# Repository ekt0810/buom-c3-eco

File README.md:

# Bướm C3 ECO

Hồ sơ prototype bướm vỗ cánh điều khiển tay bằng **XIAO ESP32-C3 + ESP-NOW**. Dự toán **3.865.000 đồng** gồm bướm, tay phát tự ráp, bộ sạc, nguồn cho sạc và 400.000 đồng dự phòng; chưa gồm dụng cụ hàn/đo. Giá và khối lượng là dự toán tại thời điểm lập hồ sơ ngày 12/11/2026.

**Chưa thử bay trên phần cứng thật.** Mạch, firmware và mô phỏng đã được kiểm tra ở mức được ghi trong báo cáo; khả năng nâng và bay cần đo trên mẫu chế tạo. Bản ECO không có IMU; PID và bám đường trong mô phỏng là phần nghiên cứu nâng cấp.

## Tải và bắt đầu

- [Tải toàn bộ hồ sơ ZIP](outputs/Buom_C3_ECO_duoi_4_trieu.zip?raw=true)
- [Hướng dẫn chế tạo PDF — 9 trang](outputs/buom_c3_eco/HUONG_DAN_CHE_TAO.pdf)
- [BOM Excel](outputs/buom_c3_eco/BOM_Buom_C3.xlsx) · [BOM CSV](outputs/buom_c3_eco/BOM.csv)
- [Đọc trước khi mua linh kiện](outputs/buom_c3_eco/README.md)
- [Báo cáo kiểm tra và giới hạn](outputs/buom_c3_eco/verification/FINAL_CHECKS.md)

## Nội dung

| Thư mục | Nội dung |
|---|---|
| [hardware](outputs/buom_c3_eco/hardware) | Schematic, PCB KiCad 10, PDF, Gerber và Excellon; carrier PCB là tùy chọn |
| [firmware_eco](outputs/buom_c3_eco/firmware_eco) | Mã Arduino cho bướm XIAO ESP32-C3 và tay phát ESP32 DevKit |
| [pid_reference](outputs/buom_c3_eco/pid_reference) | PID thuần C++ tham khảo cho nghiên cứu nâng cấp |
| [matlab](outputs/buom_c3_eco/matlab) | Mô hình MATLAB, bốn kịch bản đã chạy bằng Octave và dữ liệu kết quả |
| [viewer](outputs/buom_c3_eco/viewer) | Trình xem Three.js/WebGL 3D, thư viện đi kèm để chạy cục bộ |
| [images](outputs/buom_c3_eco/images) | Ảnh concept, sơ đồ đấu dây và ảnh xem trước |
| [verification](outputs/buom_c3_eco/verification) | Log compile, ERC/DRC, kiểm tra netlist, PID/protocol và viewer |

Firmware giao mặc định khóa actuator. Đọc hướng dẫn để điền MAC, đổi khóa ghép đôi mẫu, hiệu chuẩn nguồn/xung–góc, kiểm tra chiều servo và mất link trước khi lắp cánh.

## Chạy mô phỏng và xem 3D

Trong MATLAB, chuyển vào thư mục `outputs/buom_c3_eco/matlab` rồi chạy `run_all`. Mã không cần toolbox; kết quả đi kèm được chạy trên **GNU Octave 11.3.0**, chưa chạy trực tiếp bằng MATLAB. Hệ số khí động đang là giả định; mô hình có thông tin vị trí/độ cao lý tưởng mà phần cứng ECO không có.

Với Python 3, chạy từ thư mục gốc repo:

```sh
python outputs/buom_c3_eco/start_viewer.py
```

Trình xem tự mở tại `http://127.0.0.1:8765/viewer/`, animation tự chạy. Đây là phát lại dữ liệu mô phỏng; không phải bằng chứng mẫu thật có thể bay theo đường đó.

## Kiểm tra đã thực hiện

KiCad ERC 0 lỗi/0 cảnh báo; DRC 0 vi phạm và 0 pad chưa nối theo cấu hình kiểm tra đi kèm; đối chiếu 89 chân giữa schematic và PCB. Hai firmware đã biên dịch với Arduino-ESP32 3.3.3. Kiểm tra C++ điều khiển/protocol, bốn kịch bản Octave và viewer Edge/WebGL2 đã chạy. Các mục bỏ qua trong ERC/DRC được giữ trong file báo cáo.

[SHA256SUMS.txt](outputs/buom_c3_eco/SHA256SUMS.txt) ghi hash các file bàn giao, với đường dẫn tính từ `outputs/buom_c3_eco/`. ZIP đã được kiểm tra CRC và đối chiếu nội dung với bản thư mục.

## Nguồn cơ khí và giấy phép

Tham khảo hình học [ESP-FLUTTER của Max Imagination](https://github.com/maximagination1/ESP-FLUTTER). **File cơ khí STL có phí không nằm trong repo**; mua từ tác giả theo link trong hướng dẫn. Khoản dự toán file/in đã có trong BOM. Repo không phân phối firmware gốc của dự án tham khảo.

Xem [THIRD_PARTY.md](outputs/buom_c3_eco/THIRD_PARTY.md) và các thông báo giấy phép đi kèm cho KiCad Libraries và Three.js. Chỉ hồ sơ bàn giao và mã nguồn dự án được đưa lên đây; bộ cài, cache và file làm việc tạm không thuộc gói.

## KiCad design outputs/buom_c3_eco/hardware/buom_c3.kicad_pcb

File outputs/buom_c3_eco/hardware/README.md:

# Carrier Rev A, dùng được cho cấu hình ECO

- Kích thước 60 x 40 mm; 2 lớp; FR4 0,8 mm; 1 oz; mạ lỗ xuyên; bề mặt HASL không chì hoặc ENIG.
- XIAO hàn castellated trên 14 pad biên. Các pad BAT/debug phía đáy được bỏ có chủ ý. USB quay ra mép ngắn theo silkscreen.
- Module buck gắn ngoài qua J2. J2 không phải footprint trực tiếp của Mini-360 hoặc Pololu.
- ECO **không lắp** J3/J4/J7/Q3/R7/R8, không lắp IMU, RP1 hoặc LED. Giữ tất cả mạch nguồn, PWM và đo pin.
- J1/J2/J5/J6 có thể hàn dây trực tiếp thay header để nhẹ. Dây phải có chống kéo và kiểm tra cực. Không lấy dòng servo qua chân 5V của XIAO.
- Pad vuông là pin 1. Servo: 1=GND, 2=VSERVO, 3=PWM. Pin JST/servo ngoài thực tế phải đối chiếu, không tin màu dây.
- Q1 AO4407A S=1/2/3, G=4, D=5/6/7/8. Q2 2N7002 G=1 S=2 D=3. D1 SS14 pin1 cathode, pin2 anode.
- U2 AHCT2G125DP pin1/7=OE thấp; pin2/5=A; pin6/3=Y; pin4=GND; pin8=5V.
- C5 220uF/16V low ESR: pin1 dương, pin2 âm, đường kính thân <=6,3mm, bước chân 2,5mm.
- Đường power 1mm tối thiểu; các via chuyển lớp chính rail VSERVO được gia cường. DRC không chứng minh khả năng chịu dòng/nhiệt; đo dưới tải servo thật trước bay.
- Không có chống ngược cực. Rút pin để ngắt điện vật lý. D1 chỉ ngăn nguồn USB cấp ngược vào bus 5V bên ngoài.
- File dự án chứa cả vị trí linh kiện mở rộng để có thể dùng khi nghiên cứu PID sau. BOM chính ghi số lượng 0 cho phần bỏ lắp.

`fabrication/` dùng để gửi xưởng khi chọn làm carrier. Chỉ gửi bộ Gerber/Excellon cùng revision; không trộn với Gerber tác giả ESP-FLUTTER.

`design.json` là bảng tham chiếu Refdes/pad/net/placement. Net trong KiCad có tiền tố `/` do net local ở sheet gốc.

Thư viện `Buom.kicad_sym` và `Buom.pretty` cùng `sym-lib-table` / `fp-lib-table` cần giữ cạnh project.

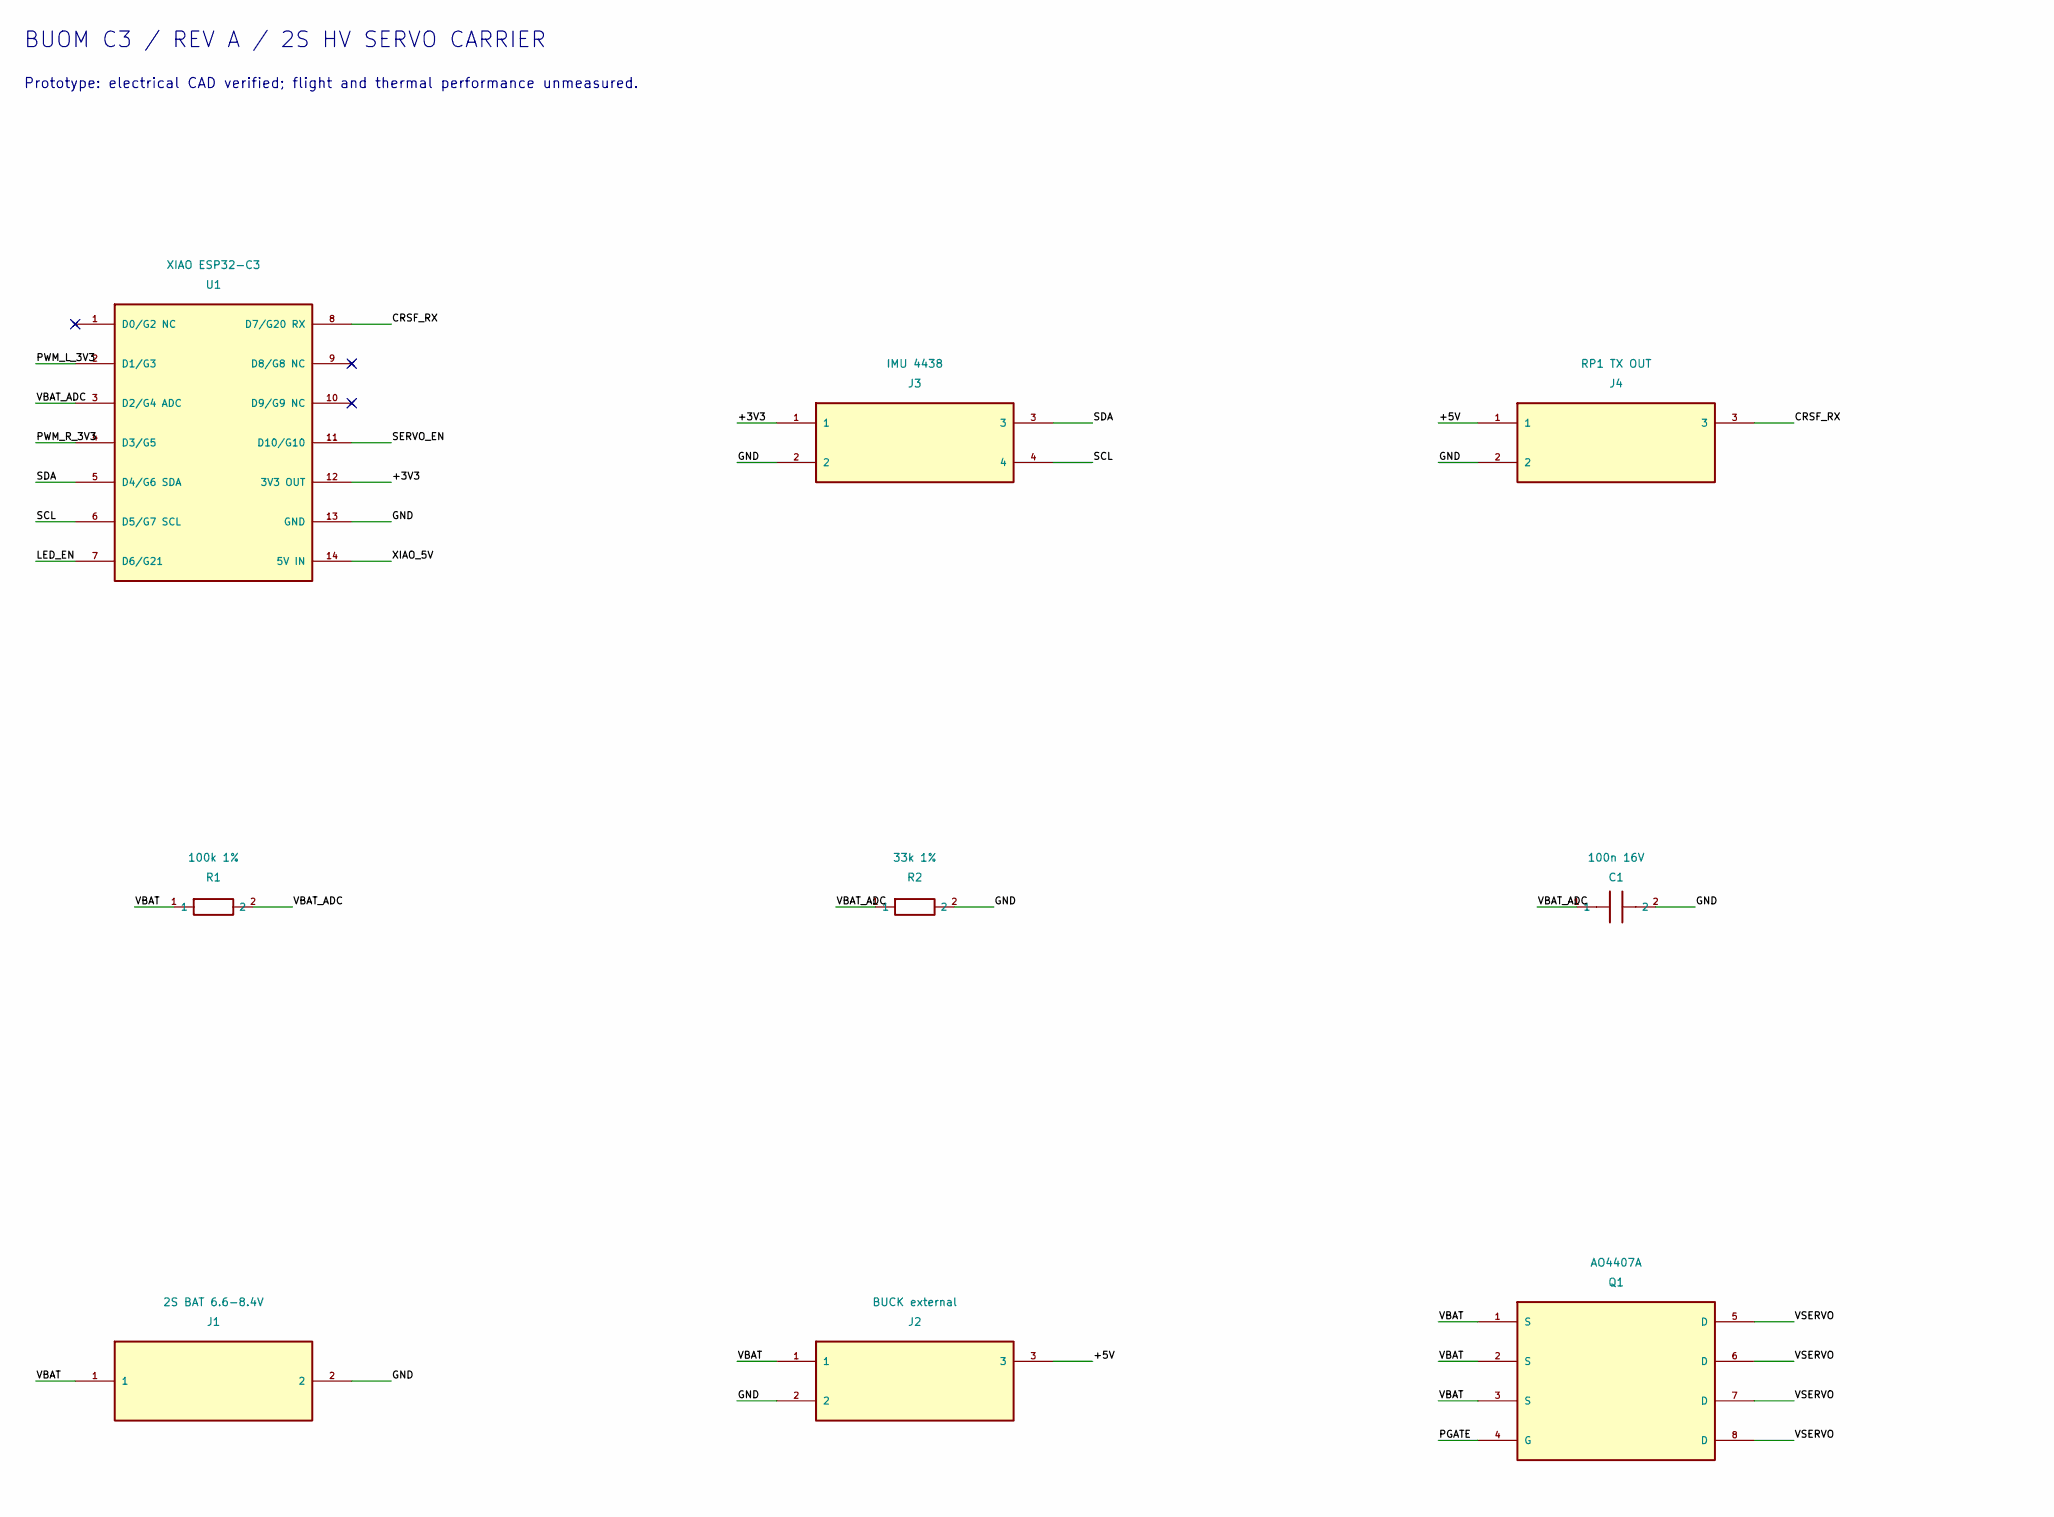
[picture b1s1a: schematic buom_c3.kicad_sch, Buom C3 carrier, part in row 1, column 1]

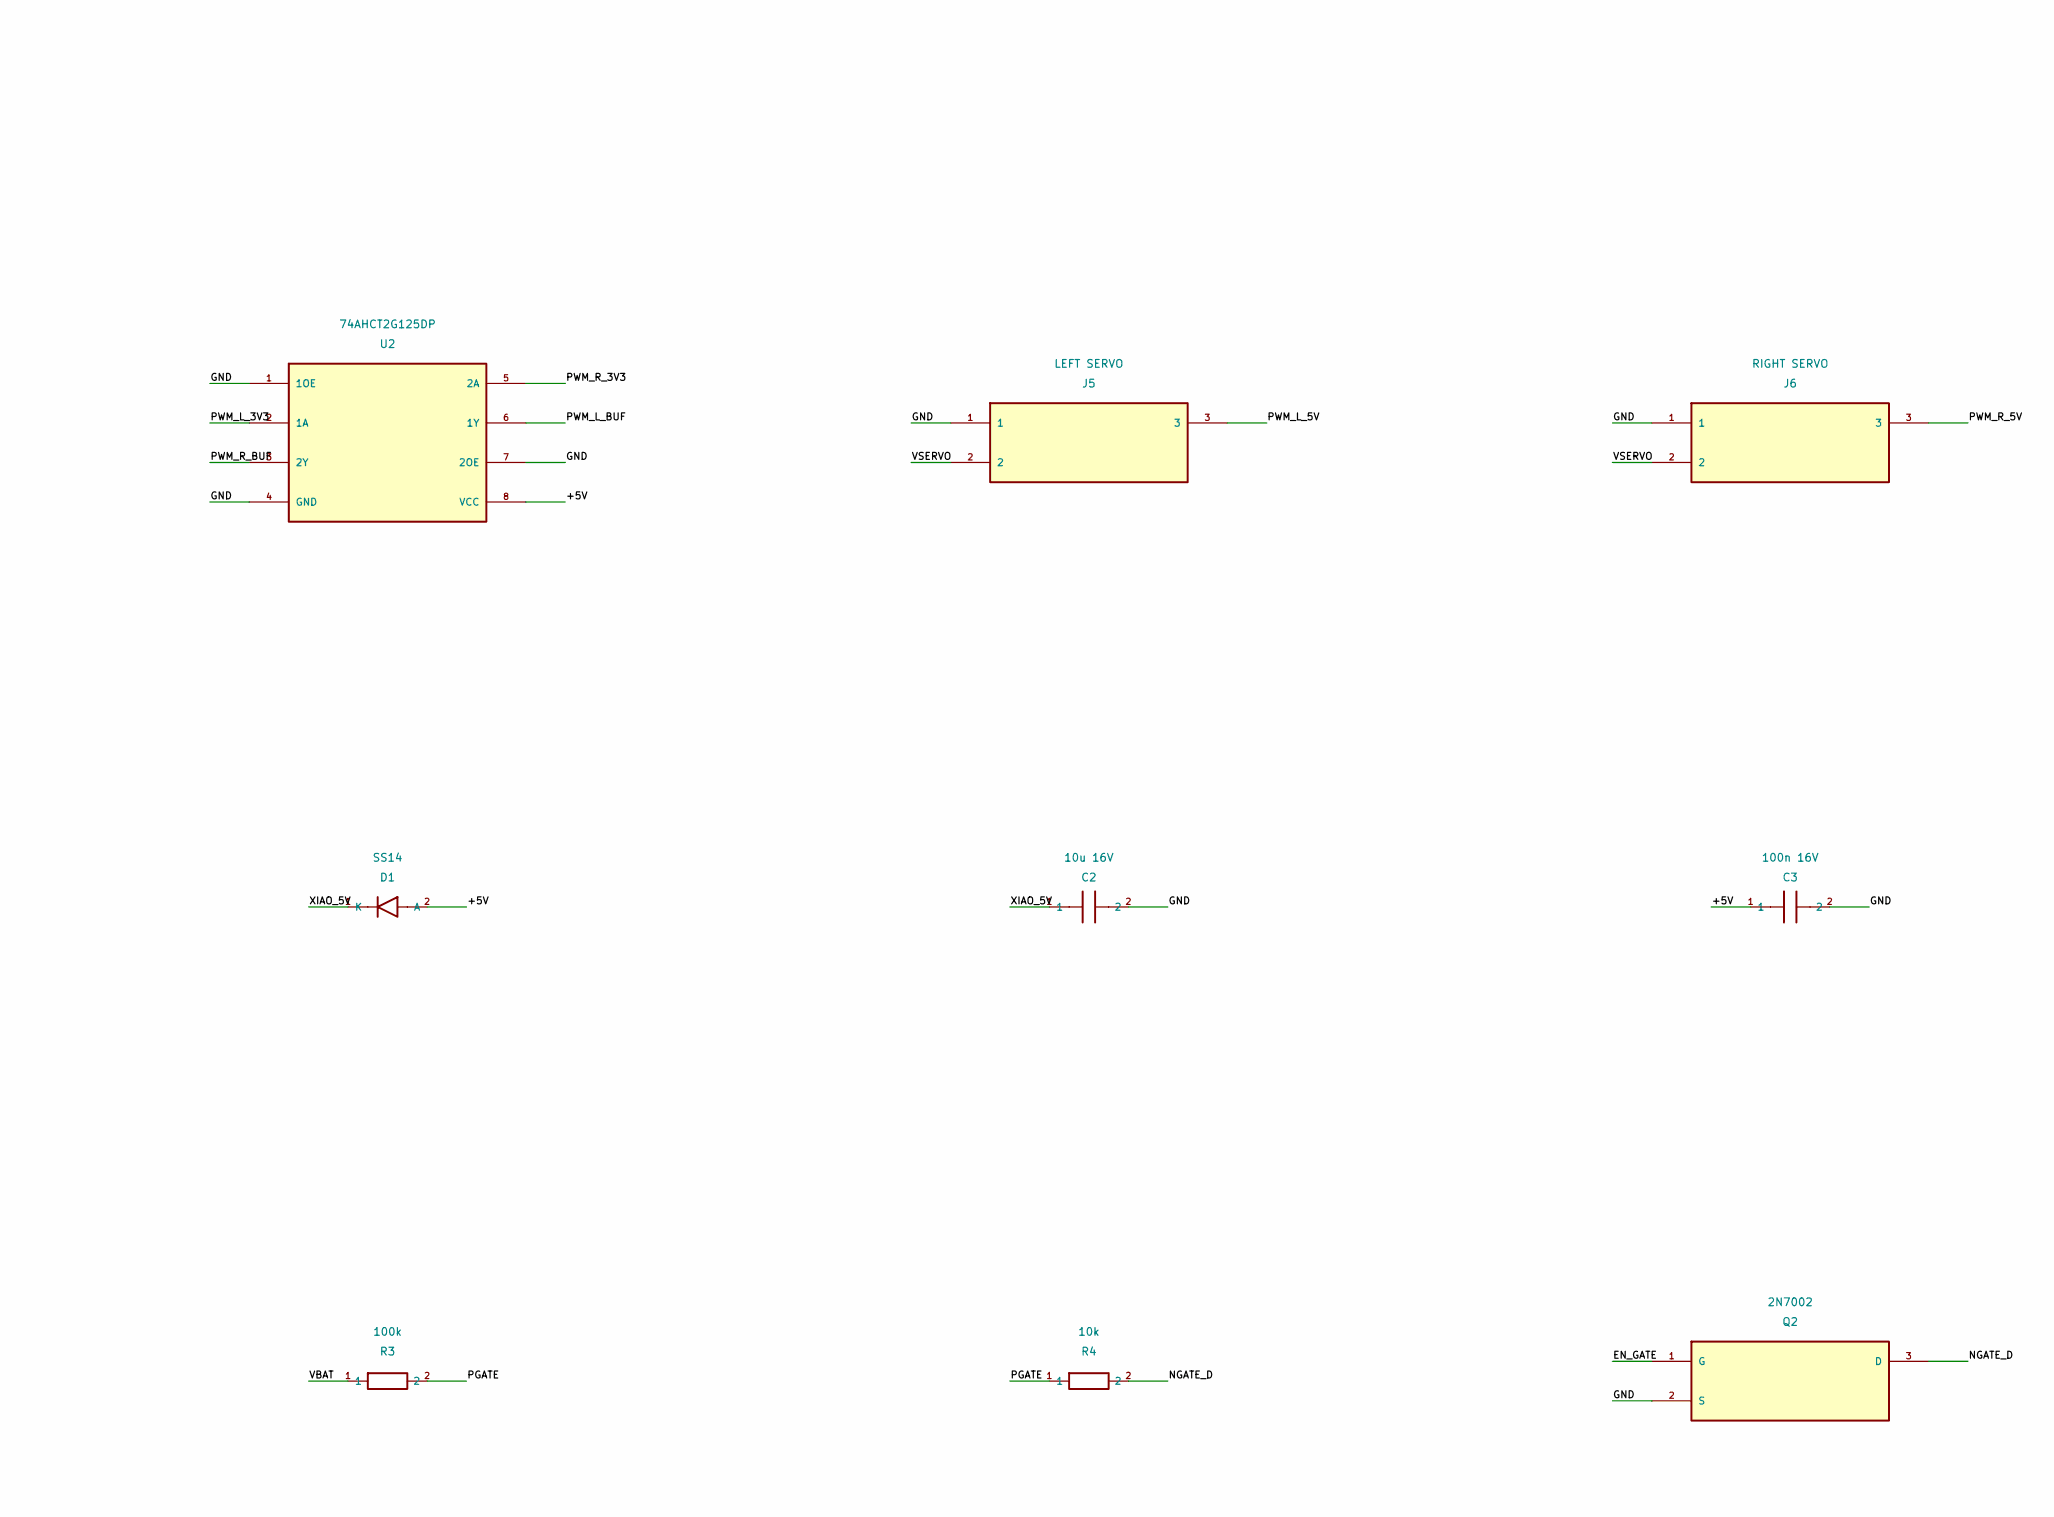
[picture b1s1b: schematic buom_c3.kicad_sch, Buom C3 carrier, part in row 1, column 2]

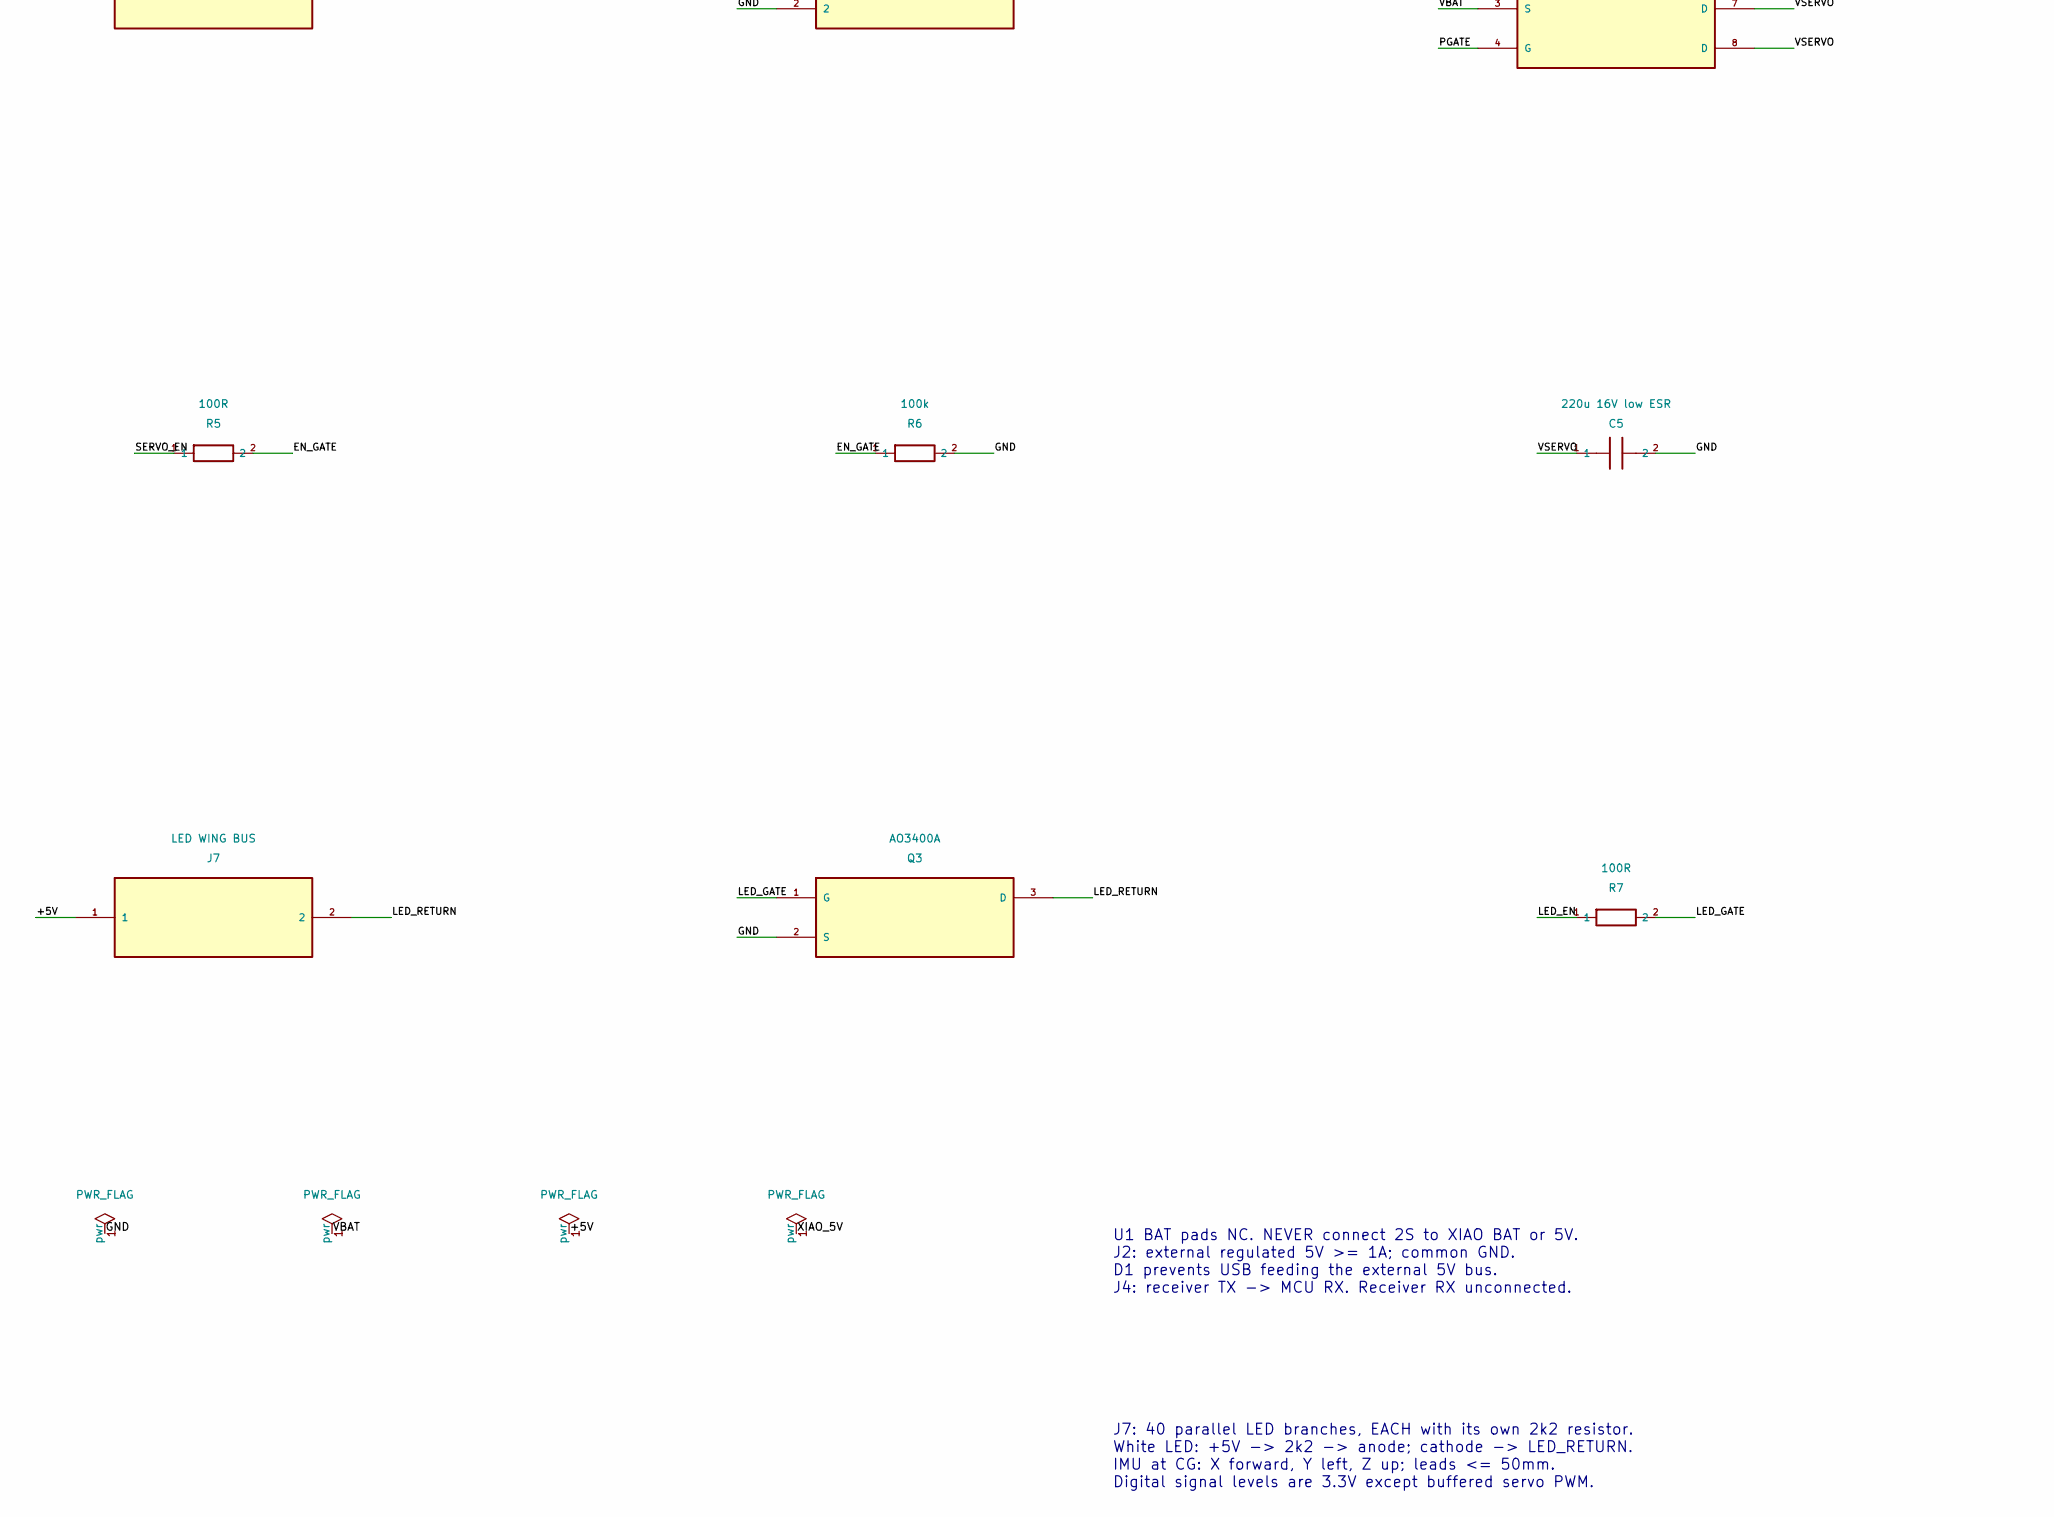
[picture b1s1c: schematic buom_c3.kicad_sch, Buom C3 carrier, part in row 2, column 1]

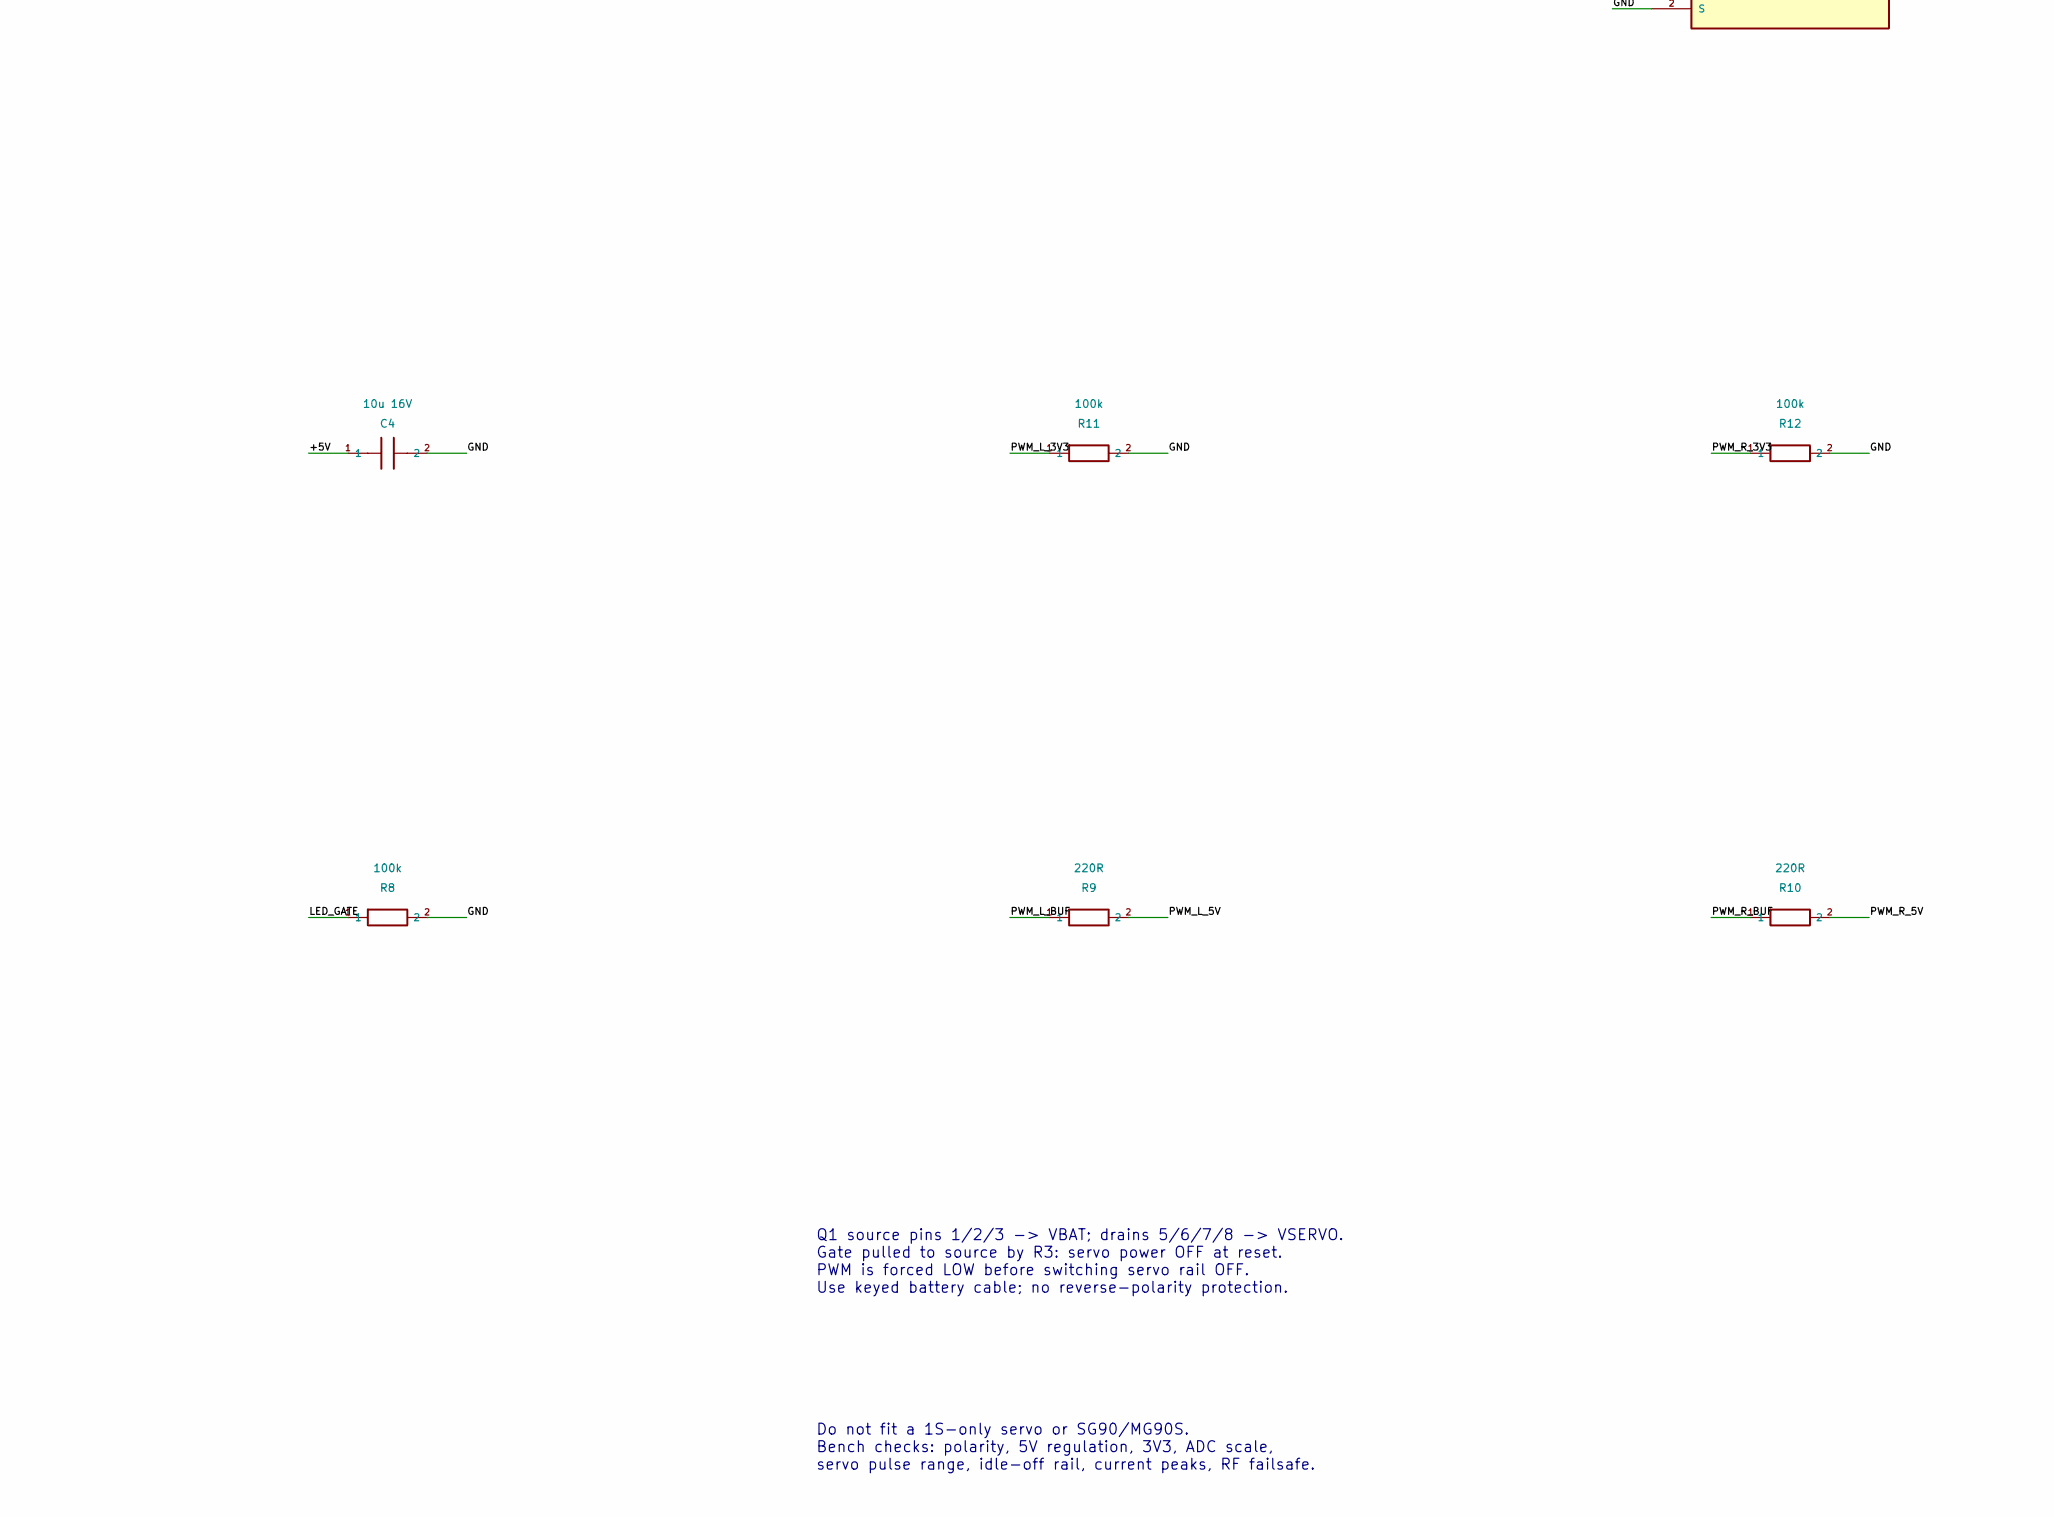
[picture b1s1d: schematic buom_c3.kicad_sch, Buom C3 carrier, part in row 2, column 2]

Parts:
C1, C3: 100n 16V; C_0805_2012Metric
C2, C4: 10u 16V; C_0805_2012Metric
C5: 220u 16V low ESR; CP_Radial_D6.3mm_P2.50mm
D1: SS14; D_SMA
J1: 2S BAT 6.6-8.4V; PinHeader_1x02_P2.54mm_Vertical
J2: BUCK external; PinHeader_1x03_P2.54mm_Vertical
J3: IMU 4438; PinHeader_1x04_P2.54mm_Vertical
J4: RP1 TX OUT; PinHeader_1x03_P2.54mm_Vertical
J5: LEFT SERVO; PinHeader_1x03_P2.54mm_Vertical
J6: RIGHT SERVO; PinHeader_1x03_P2.54mm_Vertical
J7: LED WING BUS; PinHeader_1x02_P2.54mm_Vertical
Q1: AO4407A; SOIC-8_3.9x4.9mm_P1.27mm
Q2: 2N7002; SOT-23
Q3: AO3400A; SOT-23
R1: 100k 1%; R_0805_2012Metric
R2: 33k 1%; R_0805_2012Metric
R3, R6, R8, R11, R12: 100k; R_0805_2012Metric
R4: 10k; R_0805_2012Metric
R5, R7: 100R; R_0805_2012Metric
R9, R10: 220R; R_0805_2012Metric
U1: XIAO ESP32-C3; MCU_Seeed_C3_top14
U2: 74AHCT2G125DP; TSSOP-8_3x3mm_P0.65mm

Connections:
/+3V3: J3.1, U1.12 (3V3 OUT)
/+5V: C3.1, C4.1, D1.2 (A), J2.3, J4.1, J7.1, U2.8 (VCC)
/CRSF_RX: J4.3, U1.8 (D7/G20 RX)
/EN_GATE: Q2.1 (G), R5.2, R6.1
/GND: C1.2, C2.2, C3.2, C4.2, C5.2, J1.2, J2.2, J3.2, J4.2, J5.1, J6.1, Q2.2 (S), Q3.2 (S), R2.2, R6.2, R8.2, R11.2, R12.2, U1.13 (GND), U2.1 (1OE), U2.4 (GND), U2.7 (2OE)
/LED_EN: R7.1, U1.7 (D6/G21)
/LED_GATE: Q3.1 (G), R7.2, R8.1
/LED_RETURN: J7.2, Q3.3 (D)
/NGATE_D: Q2.3 (D), R4.2
/PGATE: Q1.4 (G), R3.2, R4.1
/PWM_L_3V3: R11.1, U1.2 (D1/G3), U2.2 (1A)
/PWM_L_5V: J5.3, R9.2
/PWM_L_BUF: R9.1, U2.6 (1Y)
/PWM_R_3V3: R12.1, U1.4 (D3/G5), U2.5 (2A)
/PWM_R_5V: J6.3, R10.2
/PWM_R_BUF: R10.1, U2.3 (2Y)
/SCL: J3.4, U1.6 (D5/G7 SCL)
/SDA: J3.3, U1.5 (D4/G6 SDA)
/SERVO_EN: R5.1, U1.11 (D10/G10)
/VBAT: J1.1, J2.1, Q1.1 (S), Q1.2 (S), Q1.3 (S), R1.1, R3.1
/VBAT_ADC: C1.1, R1.2, R2.1, U1.3 (D2/G4 ADC)
/VSERVO: C5.1, J5.2, J6.2, Q1.5 (D), Q1.6 (D), Q1.7 (D), Q1.8 (D)
/XIAO_5V: C2.1, D1.1 (K), U1.14 (5V IN)

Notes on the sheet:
BUOM C3 / REV A / 2S HV SERVO CARRIER
Prototype: electrical CAD verified; flight and thermal performance unmeasured.
U1 BAT pads NC. NEVER connect 2S to XIAO BAT or 5V. J2: external regulated 5V >= 1A; common GND. D1 prevents USB feeding the external 5V bus. J4: receiver TX -> MCU RX. Receiver RX unconnected.
Q1 source pins 1/2/3 -> VBAT; drains 5/6/7/8 -> VSERVO. Gate pulled to source by R3: servo power OFF at reset. PWM is forced LOW before switching servo rail OFF. Use keyed battery cable; no reverse-polarity protection.
J7: 40 parallel LED branches, EACH with its own 2k2 resistor. White LED: +5V -> 2k2 -> anode; cathode -> LED_RETURN. IMU at CG: X forward, Y left, Z up; leads <= 50mm. Digital signal levels are 3.3V except buffered servo PWM.
Do not fit a 1S-only servo or SG90/MG90S. Bench checks: polarity, 5V regulation, 3V3, ADC scale, servo pulse range, idle-off rail, current peaks, RF failsafe.

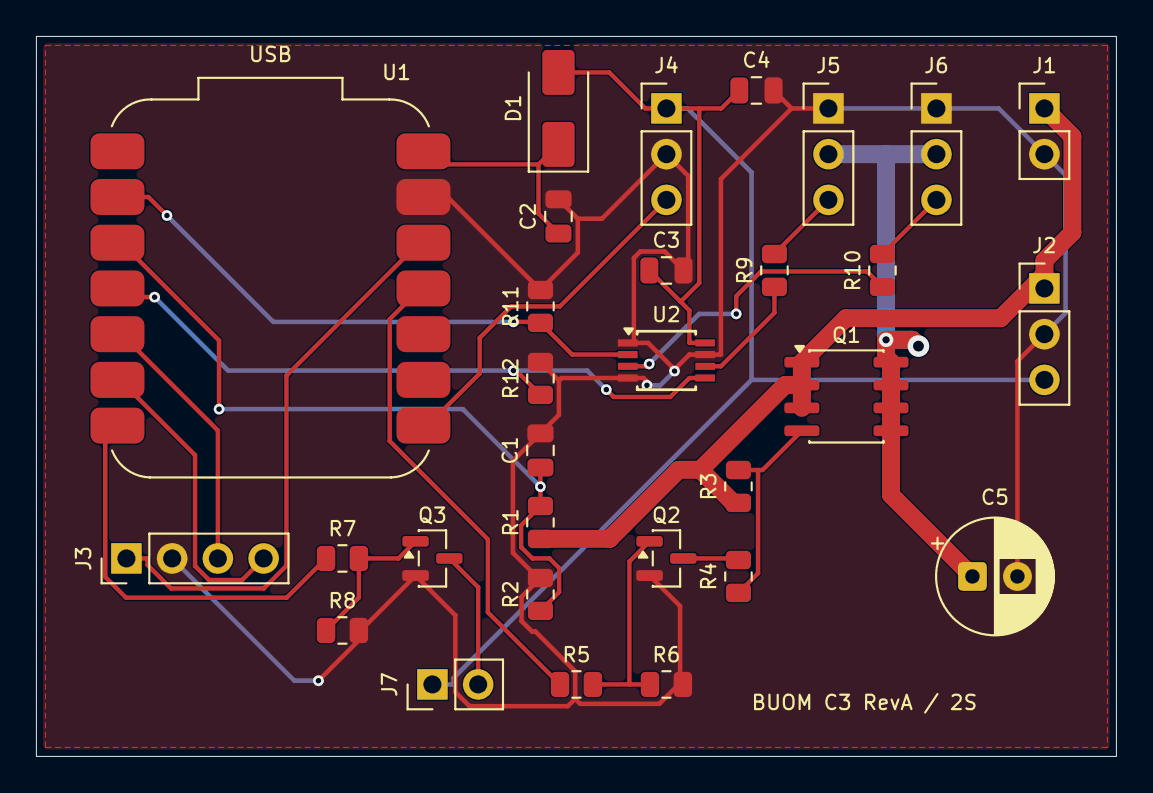
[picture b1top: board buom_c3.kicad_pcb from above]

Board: 2 copper layers, 60.0 x 40.0 mm, 30 parts (0 on the bottom side), 23 nets.
